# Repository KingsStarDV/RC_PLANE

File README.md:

# RC_PLANE

TRANSMITTER WIRING DIAGRAM--

RECEIVER WIRING DIAGRAM--

SO, As you would already have seen that the project is about a DIY RC PLANE...

**What is the RC plane?**
It is just a simple RC PLANE that i built..
It is neither inspired from any real life plane nor copied from any existing model on the internet..

**Why did you build it?**
Mainly bacause of fun but also, i saw there were little to no cheap RC PLANE BUILDS..
This build is possible with off the shelf parts and no 3D Printing..

**Parts needed**
| S.No | Component                                                         | Quantity | Unit Price (INR) | Total Price (INR) | Source            | URL                                                                                                                                                                                                                                                                                                                                                                                                                                 |
|------|-------------------------------------------------------------------|----------|------------------|-------------------|-------------------|-------------------------------------------------------------------------------------------------------------------------------------------------------------------------------------------------------------------------------------------------------------------------------------------------------------------------------------------------------------------------------------------------------------------------------------|
| 1    | ESP32 NodeMCU-32 WiFi Bluetooth Development Board (30-pin)        | 2        | 385              | 770               | Robocraze         | https://robocraze.com/products/nodemcu-32-wifi-bluetooth-esp32-development-board30-pin                                                                                                                                                                                                                                                                                                                                              |
| 2    | NRF24L01 2.4GHz PA LNA SMA Transceiver Wireless Module            | 2        | 140              | 280               | Electropi         | https://www.electropi.in/nrf24l01-2.4ghz-pa-lna-sma-transceiver-wireless-module-india                                                                                                                                                                                                                                                                                                                                               |
| 3    | KY023 2-Axis XY Analog Joystick Module                            | 2        | 25               | 50                | Robosap           | https://robosap.in/product/2-axis-xy-analog-joystick-module/                                                                                                                                                                                                                                                                                                                                                                        |
| 4    | 100uF Capacitor                                                   | 2        | 10               | 20                | Local Market      | —                                                                                                                                                                                                                                                                                                                                                                                                                                   |
| 5    | 100nF Capacitor                                                   | 2        | 10               | 29                | Local Market      | —                                                                                                                                                                                                                                                                                                                                                                                                                                   |
| 6    | Push Button                                                       | 2        | 15               | 30                | Local Market      | —                                                                                                                                                                                                                                                                                                                                                                                                                                   |
| 7    | LM2596 DC-DC Step-Down Converter Module                           | 2        | 50               | 100               | MakerBazar        | https://makerbazar.in/products/lm2596-dc-dc-converter-step-down-module                                                                                                                                                                                                                                                                                                                                                              |
| 8    | Samsung SDI INR18650 Li-Ion Rechargeable Cell                     | 2        | 250              | 500               | MakerBazar        | https://makerbazar.in/products/samsung-sdi-inr18650-li-ion-rechargeable-cells                                                                                                                                                                                                                                                                                                                                                       |
| 9    | 2S BMS + Charger Circuit (18650 Lithium Battery Protection Board) | 1        | 100              | 100               | MakerBazar        | https://makerbazar.in/products/18650-bms-lithium-battery-protection-board                                                                                                                                                                                                                                                                                                                                                           |
| 10   | AMS1117 3.3v                                                      | 1        | 15               | 15                | Local Market      | --                                                                                                                                                                                                                                                                                                                                                                                                                                  |
| 11   | BLDC Motor + ESC (30A)   [Combo Pack]                             | 1        | 840              | 840               | Flyrobo           | https://www.flyrobo.in/combo-kit-1000kv-brushless-motor-plus-30a-esc-plus-1045-propeller-pair?search=1000KV%20brushless%20                                                                                                                                                                                                                                                                                                          |
| 12   | Li-Po 3S Battery                                                  | 1        | 1320             | 1320              | Quartz Components | https://quartzcomponents.com/products/absd-11-1v-2200mah-3s-80c-lithium-polymer-rechargeable-battery?variant=45067667407082&country=IN&currency=INR&utm_medium=product_sync&utm_source=google&utm_content=sag_organic&utm_campaign=sag_organic&gad_source=1&gad_campaignid=21214248935&gbraid=0AAAAACPPFdO68kSluVmaytwAzNARdf62l&gclid=Cj0KCQjwo_PRBhDNARIsAEcVALUQSvqcWy8VqZv2AwrofMq3pP0tzYax-E9r3Mq10JGzEL9fffXafUwaAsunEALw_wcB |
| 13   | SG90 Servo Motor                                                  | 3        | 125              | 375               | Flyrobo           | https://www.flyrobo.in/sg90-9g-micro-pro-servo?tracking=ads&srsltid=AfmBOooEF27YZeO98kDfORXjG0tXWtosEH0iwh--SIsNX3iQvTPiinMiTGg                                                                                                                                                                                                                                                                                                     |
| 14   | Miscellaneous Items (tape/metal wire/wooden sticks/color etc)     | 1        | 450              | 450               | Local Market      | —                                                                                                                                                                                                                                                                                                                                                                                                                                   |
| 15   | LiPo Charger                                                      | 1        | 340              | 340               | FlyRobo           | https://www.flyrobo.in/imax-b3-lipo-balance-charger-for-2-3-cell-lipo-battery?tracking=ads&tracking=5a0a0a&gad_source=1&gad_campaignid=17418069736&gbraid=0AAAAAC6AkE8ARMj0v3RzYHIsjYuzfbWZx&gclid=Cj0KCQjwo_PRBhDNARIsAEcVALUvKASaG0qqdQnqrd34SGS2g2HuzRpHgTZcDCWmvrU8fjwtiQvCuVIaAhQ-EALw_wcB                                                                                                                                     |
| 16   | Hard Cardboard Ply                                                | 2        | 100              | 200               | Local Market      | ---                                                                                                                                                                                                                                                                                                                                                                                                                                 |
| 17   | Hardened Thermocol Sheet                                          | 2        | 50               | 100               | Local Market      | ---                                                                                                                                                                                                                                                                                                                                                                                                                                 |

**Step by step assembly instructions**

*These intructions can vary for your model.*
*You may refer to the youtube video by JakeMakes-* https://youtu.be/zVdXEjUrwiI?si=U4ZD6KPrB3ZJLI3x

Fuselage-
1) make a cuboid of (Length x Breadth x Height) of 65cm x 8cm x 7cm.
2)On one side of the cuboid (along the length), make the nose of the airplane..
3)Add a tail to the airplane of roughly 10m height.

Wings-
1)Make a 60cm x 13 cm rectangle shape out of thermocol.
2)From each side of the longer edge cut a rectangle out at a distance of 35cm..
     [Or if you didnt understood, here is a image]

3) Reattach the cut part with help of some strong tape..Remember the flap must b eable to move both up and down.

Tail Wings-
1) Similar to the wings make a rectangle of 20cm x 7cm and cut out a part for the flap..
2) similar to the wings reaatach the flap with tape leaving room for movement..

Assembly-
1)Attach the wing to the fuselage at about 17cm of distance from the extreme point of nose.
2)Secure it with rubber bands.
3)Attach the tail wings with either glue (NOT SUPER GLUE AS IT WOULD BURN THE THERMOCOL) or you can use Hot Glue..

4)Attach the Servo Motors of the wing and tail wings and make a hinge syste so that they can allow the flaps to move.
5)Attach the BLDC motor with rubber bands and place the ESC, Receiver and Batery according to the wieght distrubution, so that the plane is balanced at around the middle of wings.

6)And you are all set.

**Configure the Receiver and Transmitter**
Open the TRASMITTER code provided and set a address of your choice in the code. Remeber this address exactly.

In the reciver code, enter the same exact code.
Both the transmitter and receiver by default code are set to maximum power delivery and balanced between low latency and bandwidth.

.............................................................................................................................

## How to Upload the Code

**Requirements:**
- Arduino IDE installed
- ESP32 board package installed
- RF24 library installed

**Steps:**
1. Open Arduino IDE
2. Go to File → Open → select `transmitter.ino` (or `receiver.ino`)
3. Go to Tools → Board → select `ESP32 Dev Module`
4. Go to Tools → Port → select your COM port
5. Click the Upload button (→)
6. Repeat for the second ESP32 with the receiver code

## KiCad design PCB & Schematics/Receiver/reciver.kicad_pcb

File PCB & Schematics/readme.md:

In this folder you will find PCB and Schematic of the project..

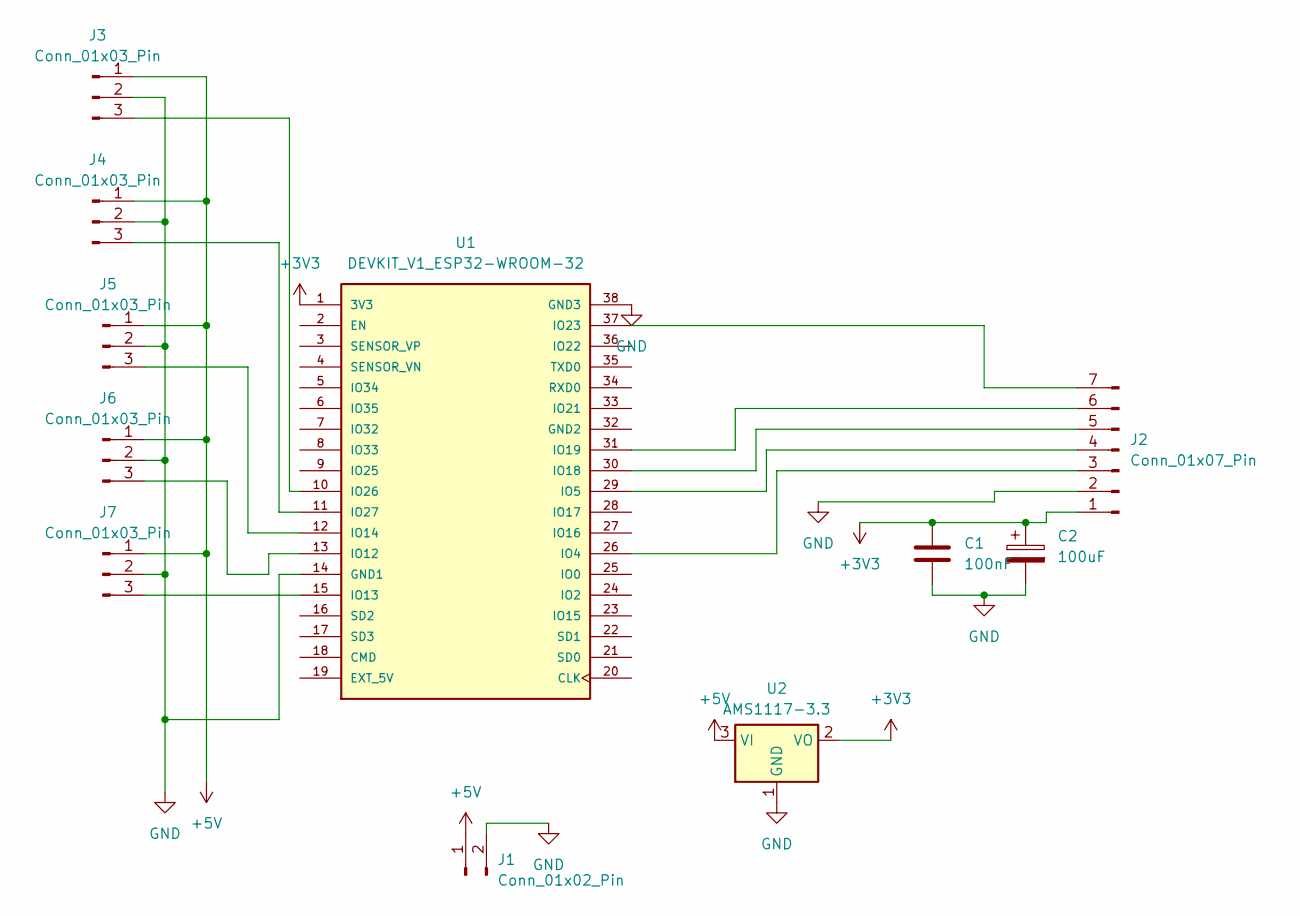
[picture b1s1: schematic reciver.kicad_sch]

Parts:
C1: 100nF; C_Disc_D3.4mm_W2.1mm_P2.50mm
C2: 100uF; CP_Radial_D5.0mm_P2.00mm
J1: Conn_01x02_Pin; PinHeader_1x02_P1.27mm_Vertical
J2: Conn_01x07_Pin; PinHeader_1x07_P2.00mm_Vertical
J3, J4, J5, J6, J7: Conn_01x03_Pin; PinHeader_1x03_P1.27mm_Vertical
U1: DEVKIT_V1_ESP32-WROOM-32; MODULE_DEVKIT_V1_ESP32-WROOM-32; PARTREV N/A
U2: AMS1117-3.3; SOT-223-3_TabPin2

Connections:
+3V3: C1.1, C2.1, J2.1, U1.1 (3V3), U2.2 (VO)
+5V: J1.1, J3.1, J4.1, J5.1, J6.1, J7.1, U2.3 (VI)
GND: C1.2, C2.2, J1.2, J2.2, J3.2, J4.2, J5.2, J6.2, J7.2, U1.14 (GND1), U1.38 (GND3), U2.1 (GND)
unnamed: J2.3, U1.26 (IO4)
unnamed: J2.4, U1.29 (IO5)
unnamed: J2.5, U1.30 (IO18)
unnamed: J2.6, U1.31 (IO19)
unnamed: J2.7, U1.37 (IO23)
unnamed: J3.3, U1.10 (IO26)
unnamed: J4.3, U1.11 (IO27)
unnamed: J5.3, U1.12 (IO14)
unnamed: J6.3, U1.13 (IO12)
unnamed: J7.3, U1.15 (IO13)

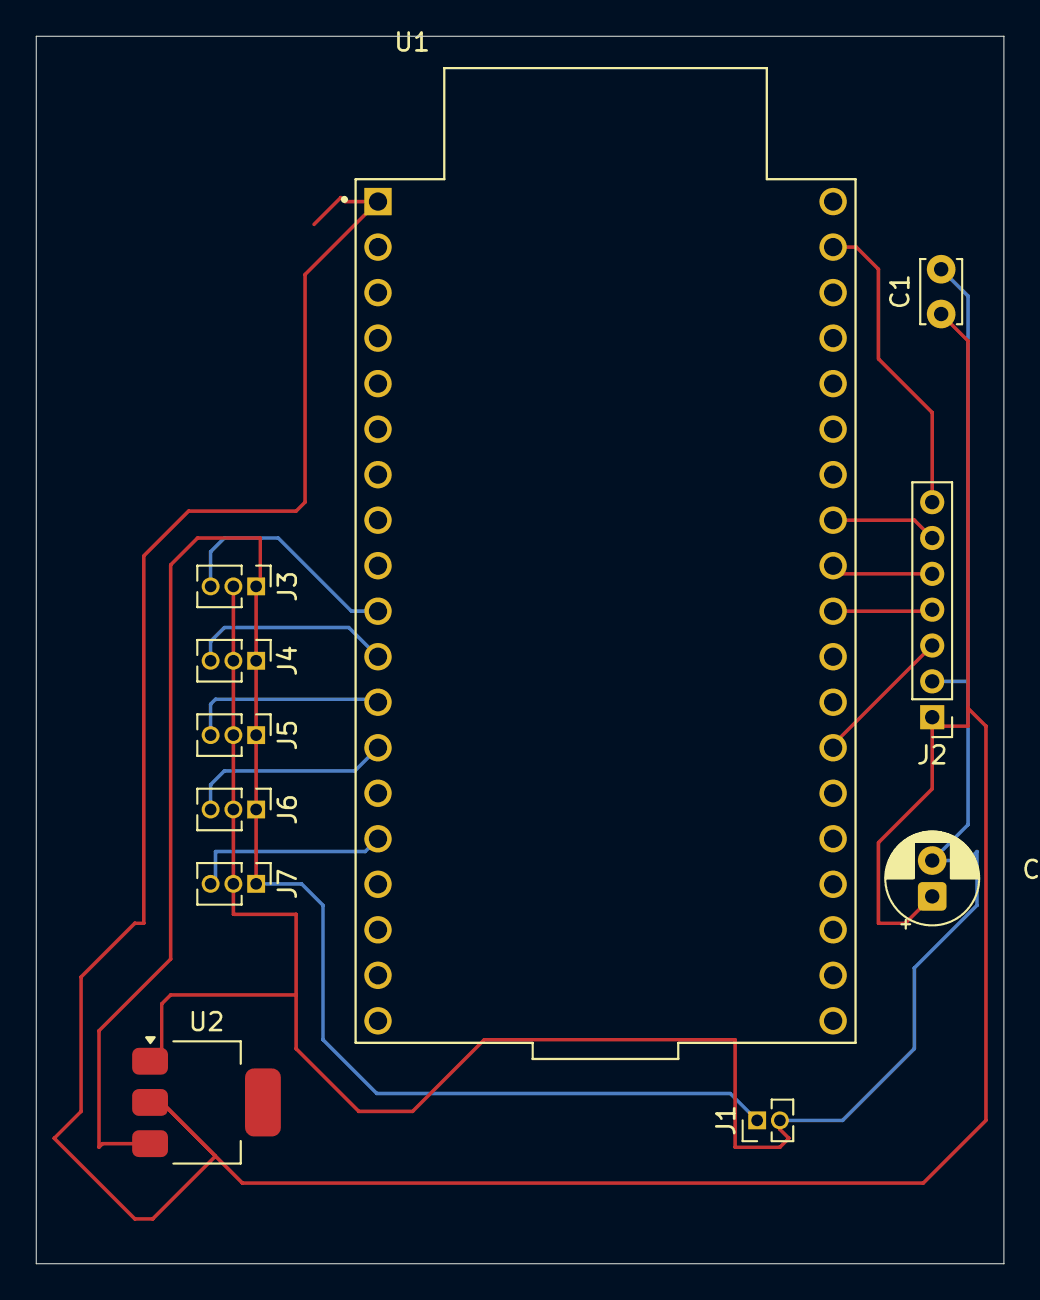
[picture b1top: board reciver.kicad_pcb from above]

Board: 2 copper layers, 54.0 x 68.5 mm, 11 parts (0 on the bottom side), 13 nets.

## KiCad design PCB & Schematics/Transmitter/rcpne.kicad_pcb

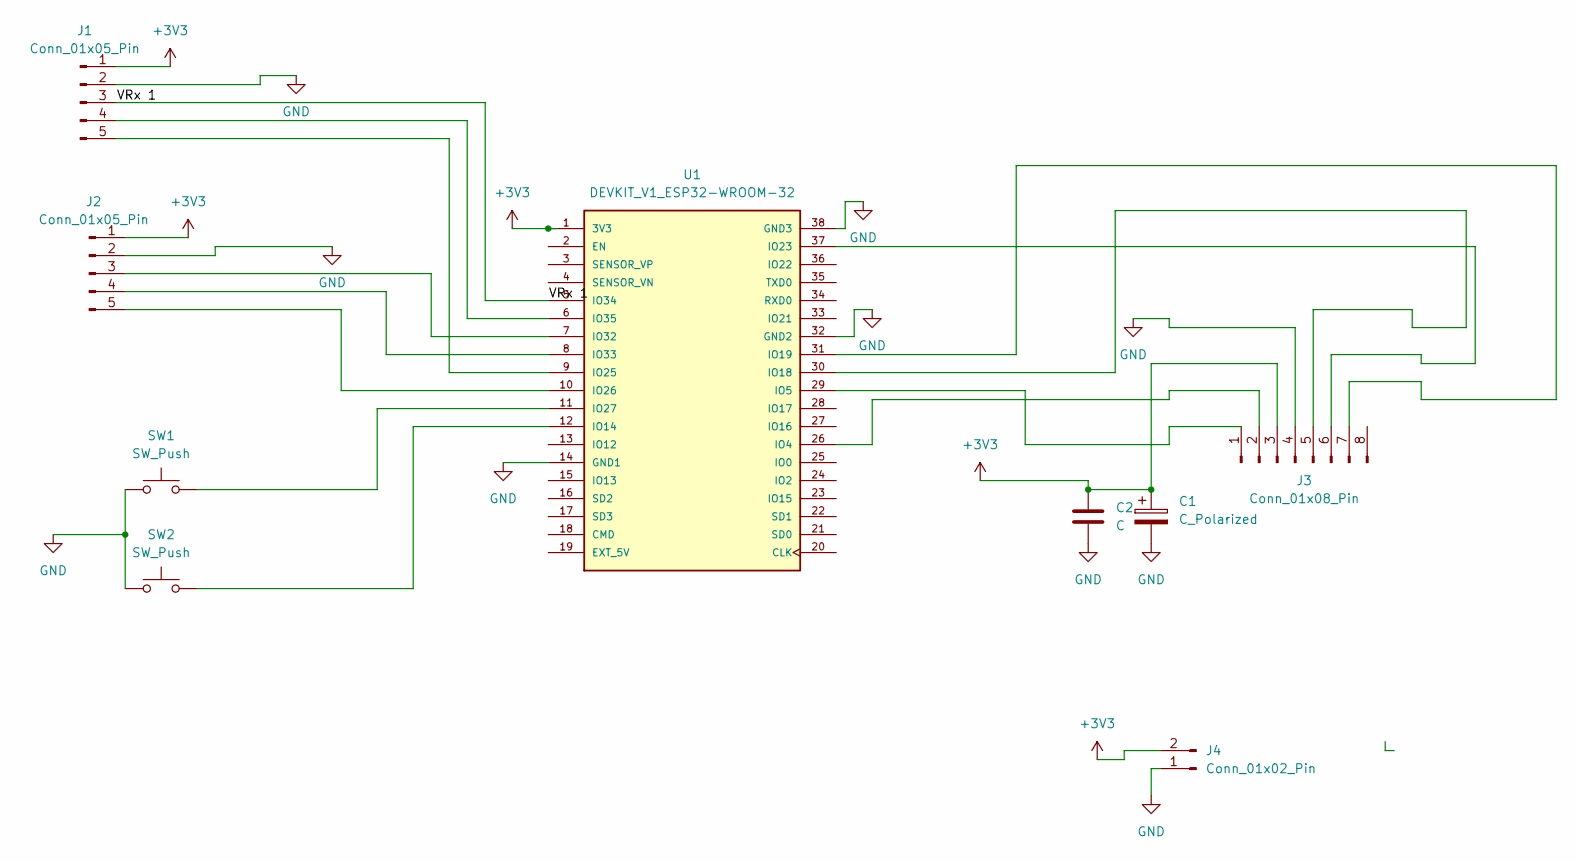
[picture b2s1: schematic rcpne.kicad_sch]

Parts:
C1: C_Polarized; CP_Radial_D6.3mm_P2.50mm
C2: C; C_Disc_D5.0mm_W2.5mm_P5.00mm
J1, J2: Conn_01x05_Pin; PinHeader_1x05_P2.00mm_Vertical
J3: Conn_01x08_Pin; PinHeader_1x08_P2.00mm_Vertical
J4: Conn_01x02_Pin; PinHeader_1x02_P2.00mm_Vertical
SW1, SW2: SW_Push; SW_TH_Tactile_Omron_B3F-100x
U1: DEVKIT_V1_ESP32-WROOM-32; MODULE_DEVKIT_V1_ESP32-WROOM-32; PARTREV N/A

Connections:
+3V3: C1.1, C2.1, J1.1, J2.1, J3.3, J4.2, U1.1 (3V3)
/VRx 1: J1.3, U1.5 (IO34)
GND: C1.2, C2.2, J1.2, J2.2, J3.4, J4.1, SW1.1, SW2.1, U1.14 (GND1), U1.32 (GND2), U1.38 (GND3)
unnamed: J1.4, U1.6 (IO35)
unnamed: J1.5, U1.9 (IO25)
unnamed: J2.3, U1.7 (IO32)
unnamed: J2.4, U1.8 (IO33)
unnamed: J2.5, U1.10 (IO26)
unnamed: J3.1, U1.29 (IO5)
unnamed: J3.2, U1.26 (IO4)
unnamed: J3.5, U1.30 (IO18)
unnamed: J3.6, U1.37 (IO23)
unnamed: J3.7, U1.31 (IO19)
unnamed: SW2.2, U1.12 (IO14)
unnamed: SW1.2, U1.11 (IO27)

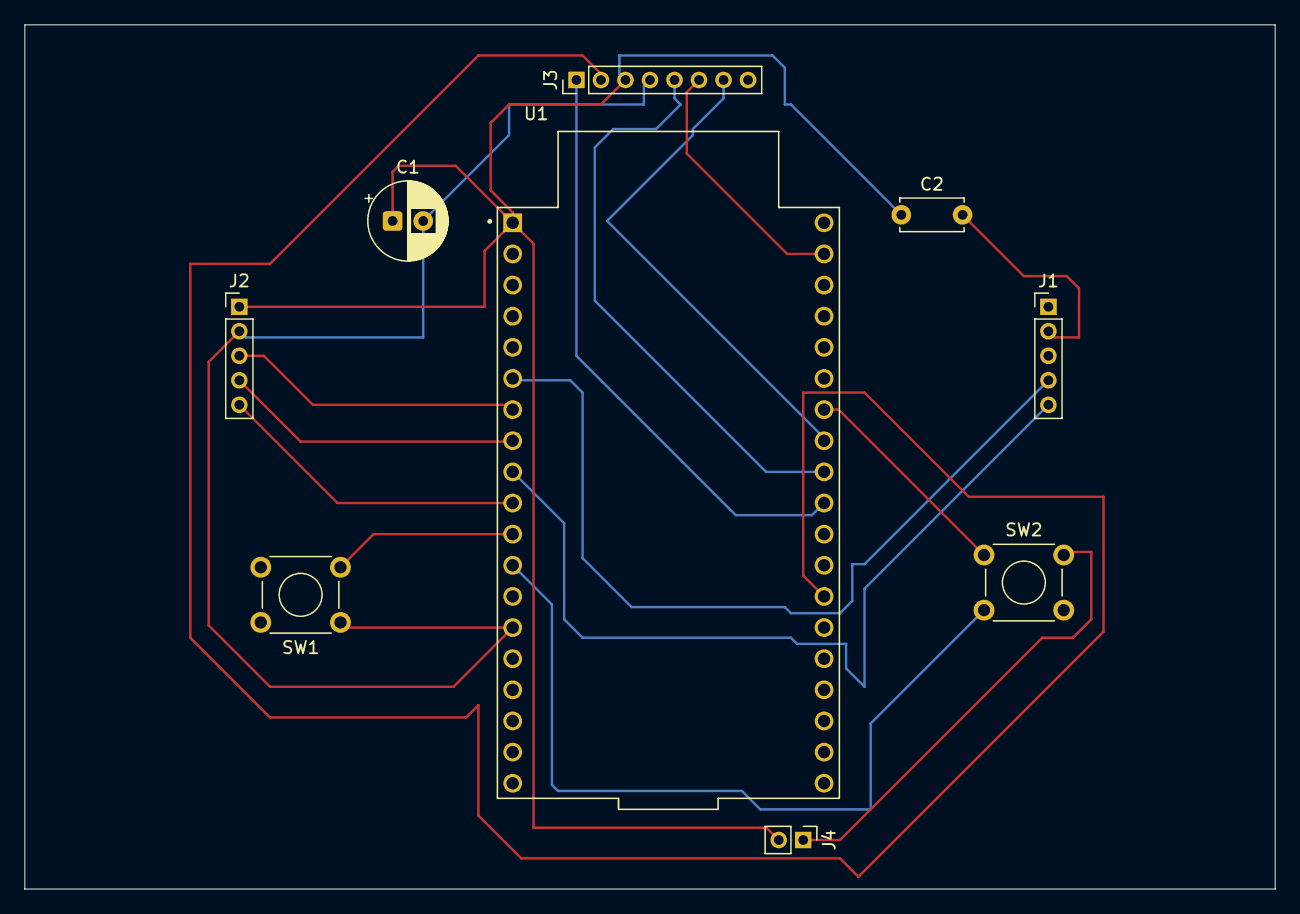
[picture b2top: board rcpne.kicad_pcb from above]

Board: 2 copper layers, 102.0 x 70.5 mm, 9 parts (0 on the bottom side), 15 nets.

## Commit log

2026-06-24 Create INGORE THIS !!
2026-06-24 Create ignore
2026-06-26 Create IGNORE THIS!!!
